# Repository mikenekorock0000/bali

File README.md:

# bali

マーダーミステリー自動進行アプリ「マダミス GM」

## 実機用 APK

**最新:** [madamis_app/dist/madamis-gm-v1.1.0+5.apk](madamis_app/dist/madamis-gm-v1.1.0%2B5.apk)（v1.1.0+5・Android WebView 修正同梱）

互換用: [madamis_app/dist/madamis-gm-release.apk](madamis_app/dist/madamis-gm-release.apk)（常に最新版と同一）

> `main` ブランチの `madamis_app/dist/` に常に置く。再ビルド時は `bash madamis_app/tool/build_release_apk.sh`

## プロジェクト

- アプリ: [madamis_app/](madamis_app/)
- 設計書: [docs/DESIGN.md](docs/DESIGN.md)
- Kindle ダッシュボード: [kindle_dashboard/](kindle_dashboard/)（Fire タブレットで YouTube ライブ・カラー版: [FIRE_SETUP.md](kindle_dashboard/FIRE_SETUP.md)）（**次にやること: [NEXT_STEPS.md](kindle_dashboard/NEXT_STEPS.md)**／NAS 設置: [NAS_SETUP.md](kindle_dashboard/NAS_SETUP.md)・[dist/](kindle_dashboard/dist/)）（調査・脱獄手順: [docs/kindle-dashboard/](docs/kindle-dashboard/README.md)）

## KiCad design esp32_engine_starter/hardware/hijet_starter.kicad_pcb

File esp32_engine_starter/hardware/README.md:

# 基板（ESP32 DevKit V1 30ピン キャリア）

**ESP32 DevKit V1 互換（30 ピン、HW-394、列間 25.4mm）を直接はんだ付けする**、2 層の基板です。部品は TVS（表面実装 4 個）以外すべてリード部品です。
38 ピンの ESP32-DevKitC はピン配置が違うので付けられません。

| 項目 | 内容 |
|---|---|
| 外形 | 98 × 90 mm（100 × 100 mm 以内なので JLCPCB の最安価格）、角に M3 取付穴 ×4 |
| 部品 | 抵抗・ダイオードは足の間隔 5.08 mm で立てて実装。出力の TVS だけ表面実装（SMB、はんだごてで付けられる大きさ） |
| ESP32 | ソケットを使わず直接はんだ付け（振動でソケットが緩むのを防ぐ）。ESP32 の下（隙間 約 2.5mm）には部品を置かない |
| 層 | 2 層（両面に GND ベタ） |
| 最小パターン幅 / 間隔 | 0.4 mm / 0.3 mm（電源系は 1.0 mm） |
| 最小穴径 | 0.4 mm（ビア） |
| 検証 | DRC・ピン照合・部品の収まり・回路シミュレーション・製造データ照合すべて合格。詳しくは [VERIFICATION.md](VERIFICATION.md) |

## 発注するファイル

- **`hijet_starter_gerber.zip`** … ガーバー＋ドリル一式。JLCPCB などにそのままアップロードします。
- 発注時の設定：2 層、FR-4、板厚 1.6 mm、銅厚 1 oz、表面処理は HASL（鉛フリー）、レジストは緑、シルクは白。
- **部品表 `bom.csv`** … 部品ごとに秋月電子通商の商品ページの URL と、買う数を載せています（全部品が秋月でそろいます）。

> **発注前に必ず確認してください。** `hijet_starter_1to1.pdf` を**原寸（100%・拡大縮小なし）**で印刷し、
> 実物の ESP32 ボードのピンが J5・J6 の穴の位置に合うこと、端子台・ブザー・DC-DC の足が穴に合うことを確かめてください。
> 列の間隔 25.4 mm は、購入したボードをノギスで測った値（外側どうし 26.0 mm）と一致しています。

## 回路

| ブロック | 内容 |
|---|---|
| 電源 | J1「+12V」→ F1 ポリスイッチ MF-RX110/72 または RXEF110（1.1A・72V）→ D1 SB340LS（3A、逆接保護）→ D2 P4KE15A ＋ D12 P4KE6.8CA（直列でサージ吸収）・C1 100µF 50V → U1 M78AR05-1（5V 1A、入力 6.5〜32V）→ C2 100µF・C3 0.1µF → ESP32 の 5V ピン |
| 電圧測定 | ヒューズの後ろの 12V → R1 100k / R2 10k で分圧 → GPIO34（16V で 1.45V、9V で 0.82V＝ADC の精度のよい範囲内）。C4 0.1µF でノイズ除去、D3 BAT43 で 3.3V を超えないようクランプ |
| 絶縁出力 ×4 | GPIO25 / 26 / 27 / 32 → 330Ω → PC817（U2〜U5、VCEO 80V）の LED。トランジスタ側を J2 に出す（ESP32 とは電気的に絶縁、各 50mA 以下）。**端子の 2 本の間に双方向 TVS SMBJ45CA（D8〜D11）** |
| 絶縁入力 ×3 | J3 の IN+ → 3.3k → PC817（U6〜U8）→ IN−。1N4148 で逆電圧を保護。出力は GPIO33 / GPIO35 / GPIO36（10k で 3.3V にプルアップ、信号ありで LOW）。3ch 目は ACC（キー ON）検知用。35V まで耐える |
| OBD-II（CAN） | MCP2562FD（U9）。VDD=5V、VIO=3.3V。TXD=GPIO18、RXD=GPIO19。STBY は R15 10k で 3.3V に引いて**既定は待機（車の CAN に一切関与しない）**、GPIO4 を LOW にしたときだけ動作。CAN-H / CAN-L を J7 へ（終端抵抗は付けない） |
| ブザー | GPIO13 → R13 1k → 2SC1815 → 5V 自励式ブザー。R14 10k で起動時は確実に OFF、D7 1N4148 で逆起電力を吸収 |
| GPS | J8：GND / 3V3 / GPS RX（GPIO17 から）/ GPS TX（GPIO16 へ） |
| I2C | J4：GND / 3V3 / SCL(GPIO22) / SDA(GPIO21)。0.96 インチ OLED（SSD1306）モジュールと同じピンの並び |

### 車載向けの保護

| 想定するもの | 対策 |
|---|---|
| バッテリーの逆接続 | D1 SB340LS が電流を止める。入力は 1N4148 で LED を守る。電圧測定は R1 100k で電流を制限 |
| 配線のショート・過電流 | F1 ポリスイッチ（自己復帰型）。トリップするまでの最大 2.2A を流しても D1（3A）は耐える。車両側にもヒューズを入れる |
| 電源ラインのサージ（ノイズ、オルタネーターの急な負荷変動） | D2 P4KE15A と D12 P4KE6.8CA の直列で約 30V 以下に抑える（DC-DC の上限 32V）。18.6V までは導通しない。長く続くときは F1 が切れて止まる |
| 出力の配線から入るサージ、リレーのコイルの逆起電力 | D8〜D11 SMBJ45CA（双方向）が 72.7V 以下に抑える（フォトカプラの上限 80V） |
| 入力の配線のサージ | 3.3k で電流を制限（35V でも LED 10mA、抵抗の発熱は短時間の許容内） |
| 振動 | ESP32 をソケットでなく直接はんだ付け。電解コンデンサは背の低いもの（C2）を使う。基板は M3 スペーサー 4 本で固定 |

**守れないもの**：24V でのジャンプスタート（トラック用の救援）では D2 が導通して F1 が切れ、装置は止まります（壊れるのを防ぐ動作）。続くと D2 が壊れることがあり、その場合は D2 を交換します。

## 端子の使い方

端子台はすべて 5.08mm ピッチです。J2 は 2P を 4 個、J3 は 2P を 3 個、横にスライドさせて連結してから基板に挿します。

| 端子 | ピン | つなぐ先 |
|---|---|---|
| J1 | +12V | ヒューズ電源（常時電源）。車両側にもヒューズを入れる |
|  | GND | ボディアース |
|  | OUT | ヒューズ通過後の 12V（予備入力の IN+ 用） |
| J2 | LOCK − / + | 車両の施錠信号（GND に落とすと施錠するタイプ）。＋を信号線、−を GND へ。線は配線図か取付店で必ず確認する。**＋と−を逆につながない**（フォトカプラは逆向きの電圧に 6V までしか耐えない） |
|  | OUT2〜OUT4 − / + | 汎用。作業灯などはリレーモジュールの入力につなぐ（直接は駆動できない） |
| J3 | IN1 + / − | 例：ドアの開閉信号（スイッチが GND に落ちるタイプ）は、IN+ を J1 の「OUT」へ、IN− をドアの信号線へつなぐ |
|  | ACC + / − | ACC（キー ON で 12V）の線を ACC+ に、ACC− を GND に |
| J7 | CAN H / L / G | OBD-II コネクタの 6 番（CAN-H）、14 番（CAN-L）、4・5 番（GND）。市販の OBD-II 延長ケーブルを切って使うと楽 |
| J8 | GND 3V3 GPS RX / TX（上から） | NEO-6M など UART の GPS モジュール。GPS RX の端子をモジュールの RX に、GPS TX の端子をモジュールの TX につなぐ |
| J4 | GND 3V3 SCL SDA（上から） | OLED や温度センサー（BME280 など）。四角いパッドが GND |

## 組み立て

部品表は `bom.csv` です。部品番号は基板のシルク印刷と同じです。

1. **最初に TVS（D8〜D11）** を付けます。表面実装なので、片方のパッドに少しはんだを盛り、ピンセットで部品を押さえて温め、反対側を付けます。向きはありません（双方向）。
2. 背の低い部品から順にはんだ付けします：抵抗 → ダイオード → フォトカプラ・MCP2562 → セラミックコンデンサ → トランジスタ → ピンヘッダー（J4・J8）→ ポリスイッチ → 電解コンデンサ → ブザー → 端子台 → DC-DC。
3. **向きのある部品に注意してください。**
   - ポリスイッチ（F1）：本体が大きい（幅 12.8mm）ので、基板の上の端に横向きに付ける。向きはない。
   - ダイオード（D1〜D7、D12）：立てて付ける。本体を丸いシルクの穴の上に立て、**帯（カソード）を上にして**、上から折り返した足を「K」の四角いパッドへ。D12（P4KE6.8CA）だけは双方向なので向きはどちらでもよい。
   - 電解コンデンサ（C1・C2）：長い足（＋）を、シルクの「+」がある四角いパッドに。
   - フォトカプラ（U2〜U8）：本体の 1 番ピンの丸印を、四角いパッドに合わせる。
   - M78AR05-1（U1）：1 番ピン（Vin）を四角いパッドに。
   - MCP2562（U9）：本体の 1 番ピンの丸印（切り欠き側）を四角いパッドに。
   - 2SC1815（Q1）：左のパッドから E-C-B。シルクの半円が本体の丸い側。足の並びが違うトランジスタは使わない。
   - 抵抗：立てて付ける。どちら向きでもよい（本体を丸いシルクの穴の上に立てる）。
   - ブザー（BZ1）：＋表示の足（長い足）を「+」の四角いパッドに。
4. **ESP32 を付ける前に**、J1 に 12V をつないで、J5 の 15 番ピン（いちばん下、ESP32 の VIN）と GND の間が約 5V になることをテスターで確認します。
5. ESP32 ボードを **USB コネクタが基板の下側（「USB cable keep clear」の文字の方）**、VIN の列が左（J5）に来る向きで挿し、ボードを基板に押し付けたまま（ピンの樹脂が基板に当たるまで）四隅のピンを先にはんだ付けしてから、残りのピンを付けます。直接はんだ付けなので、後から外すのは大変です。向きを 2 回確かめてから付けてください。
6. ESP32 に USB で書き込むときは、J1 の 12V を外してください（両方から同時に給電しないため）。USB ケーブルのプラグは基板の上を通るので、「USB cable keep clear」の場所には何も置かないでください。

## 作り直すとき

`./build.sh` は、生成のあとに DRC・ピン照合（`check_pins.py`）・部品の収まり（`check_mech.py`）・回路シミュレーション（`sim/`、ngspice が必要）・製造データ照合（`check_fab.py`）を実行し、1 つでも問題があれば止まります。

```
./build.sh   # 生成 → 検証（DRC・ピン・収まり・回路・製造データ）→ ガーバー/ドリル → zip → BOM → 原寸 PDF → プレビュー
```

KiCad 7（`kicad-cli` と Python の `pcbnew`）と numpy が必要です。部品の位置と接続先は `gen_pcb.py` の上の方にまとめてあります。
配線は簡易オートルーターで引いているので、部品を動かしたら必ず `./build.sh` で DRC を通してください。

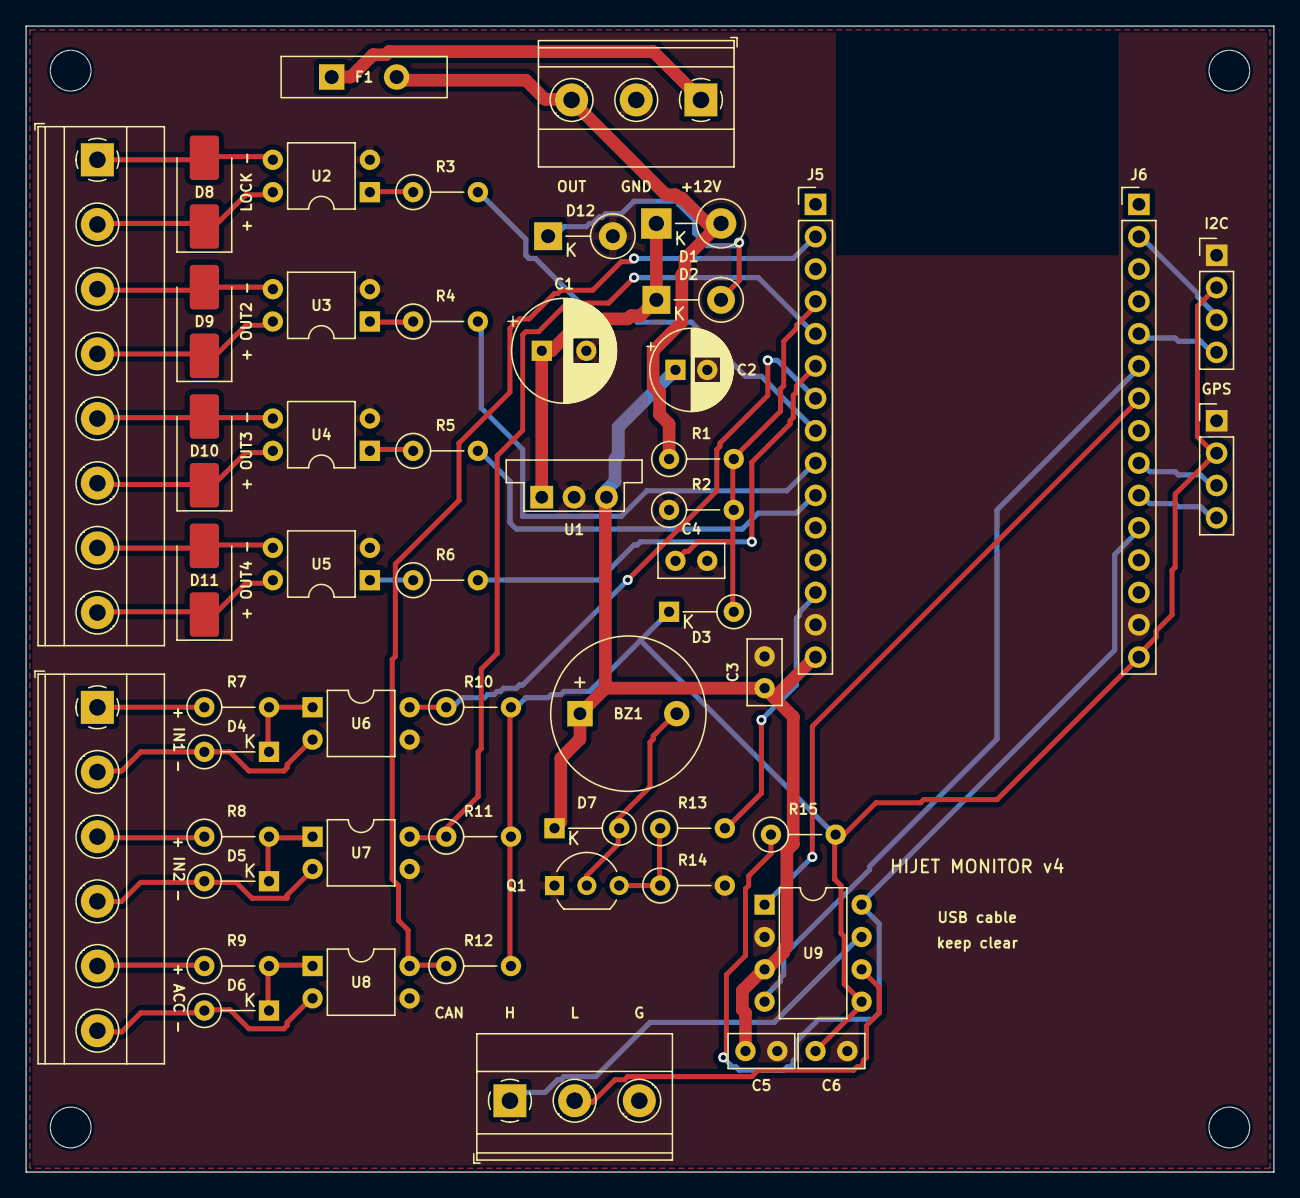
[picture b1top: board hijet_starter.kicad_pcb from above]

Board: 2 copper layers, 98.0 x 90.0 mm, 57 parts (0 on the bottom side), 48 nets.

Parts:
BZ1: Buzzer 5V 12mm; Buzzer_12x9.5RM7.6
C1: 100uF 50V; CP_Radial_D8.0mm_P3.50mm
C2: 100uF 16V; CP_Radial_D6.3mm_P2.50mm
C3, C4, C5, C6: 0.1uF; C_Disc_D5.0mm_W2.5mm_P2.50mm
D1: SB340LS; D_DO-15_P5.08mm_Vertical_KathodeUp
D2: P4KE15A; D_DO-41_SOD81_P5.08mm_Vertical_KathodeUp
D3: BAT43; D_DO-35_SOD27_P5.08mm_Vertical_KathodeUp
D4, D5, D6, D7: 1N4148; D_DO-35_SOD27_P5.08mm_Vertical_KathodeUp
D8, D9, D10, D11: SMBJ45CA; D_SMB_Handsoldering
D12: P4KE6.8CA; D_DO-41_SOD81_P5.08mm_Vertical_KathodeUp
F1: PTC 1.1A; PTC_Radial_W12.8mm_T3.0mm_P5.10mm
H1, H2, H3, H4: M3; MountingHole_3.2mm_M3
J1: 12V IN; TerminalBlock_Phoenix_MKDS-1,5-3-5.08_1x03_P5.08mm_Horizont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
J2: OUT; TerminalBlock_Phoenix_MKDS-1,5-8-5.08_1x08_P5.08mm_Horizont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
J3: IN; TerminalBlock_Phoenix_MKDS-1,5-6-5.08_1x06_P5.08mm_Horizont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
J4: I2C; PinHeader_1x04_P2.54mm_Vertical
J5: ESP32 VIN row; PinHeader_1x15_P2.54mm_Vertical
J6: ESP32 3V3 row; PinHeader_1x15_P2.54mm_Vertical
J7: OBD-II CAN; TerminalBlock_Phoenix_MKDS-1,5-3-5.08_1x03_P5.08mm_Horizont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
J8: GPS; PinHeader_1x04_P2.54mm_Vertical
Q1: 2SC1815; TO-92_Inline_Wide
R1: 100k; R_Axial_DIN0207_L6.3mm_D2.5mm_P5.08mm_Vertical
R2, R10, R11, R12, R14, R15: 10k; R_Axial_DIN0207_L6.3mm_D2.5mm_P5.08mm_Vertical
R3, R4, R5, R6: 330; R_Axial_DIN0207_L6.3mm_D2.5mm_P5.08mm_Vertical
R7, R8, R9: 3.3k; R_Axial_DIN0207_L6.3mm_D2.5mm_P5.08mm_Vertical
R13: 1k; R_Axial_DIN0207_L6.3mm_D2.5mm_P5.08mm_Vertical
U1: M78AR05-1; Converter_DCDC_Murata_OKI-78SR_Vertical
U2, U3, U4, U5, U6, U7, U8: PC817; DIP-4_W7.62mm
U9: MCP2562-E/P; DIP-8_W7.62mm

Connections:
12V_F: D1.2, F1.2, J1.3, R1.1
12V_P: C1.1, D1.1, D2.1, U1.1
+3V3: C6.1, D3.1, J4.2, J6.15, J8.2, R10.2, R11.2, R12.2, R15.2, U9.5
+5V: BZ1.1, C2.1, C3.1, C5.1, D7.1, J5.15, U1.3, U9.3
BATT: F1.1, J1.1
BZN: BZ1.2, D7.2, Q1.2
CANH: J7.1, U9.7
CANL: J7.2, U9.6
G13: J5.13, R13.2
G16: J6.10, J8.4
G17: J6.9, J8.3
G18: J6.7, U9.1
G19: J6.6, U9.4
G25: J5.8, R3.2
G26: J5.9, R4.2
G27: J5.10, R5.2
G32: J5.6, R6.2
G33: J5.7, R10.1, U6.4
G35: J5.5, R11.1, U7.4
G36: J5.2, R12.1, U8.4
GND: C1.2, C2.2, C3.2, C4.2, C5.2, C6.2, D12.2, J1.2, J4.1, J5.14, J6.14, J7.3, J8.1, Q1.1, R2.1, R14.2, U1.2, U2.2, U3.2, U4.2, U5.2, U6.3, U7.3, U8.3, U9.2
IN1A: D4.1, R7.2, U6.1
IN1N: D4.2, J3.2, U6.2
IN1P: J3.1, R7.1
IN2A: D5.1, R8.2, U7.1
IN2N: D5.2, J3.4, U7.2
IN2P: J3.3, R8.1
IN3A: D6.1, R9.2, U8.1
IN3N: D6.2, J3.6, U8.2
IN3P: J3.5, R9.1
LED1: R3.1, U2.1
LED2: R4.1, U3.1
LED3: R5.1, U4.1
LED4: R6.1, U5.1
O1C: D8.1, J2.2, U2.4
O1E: D8.2, J2.1, U2.3
O2C: D9.1, J2.4, U3.4
O2E: D9.2, J2.3, U3.3
O3C: D10.1, J2.6, U4.4
O3E: D10.2, J2.5, U4.3
O4C: D11.1, J2.8, U5.4
O4E: D11.2, J2.7, U5.3
QB: Q1.3, R13.1, R14.1
SCL: J4.3, J6.2
SDA: J4.4, J6.5
STBY: J6.11, R15.1, U9.8
TVSM: D2.2, D12.1
VSENSE: C4.1, D3.2, J5.4, R1.2, R2.2

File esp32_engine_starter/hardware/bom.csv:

部品数,部品番号,値,内容,買う数,購入先,URL
1,BZ1,Buzzer 5V 12mm,電子ブザー（発振回路内蔵）5V φ12mm UGCM1205XP。足の間隔 7.6mm を原寸 PDF で確認,1,秋月,https://akizukidenshi.com/catalog/g/g109800/
1,C1,100uF 50V,電解コンデンサ 100µF 50V φ8mm 足の間隔 3.5mm（105℃、Rubycon PX）,1,秋月,https://akizukidenshi.com/catalog/g/g117905/
1,C2,100uF 16V,電解コンデンサ 100µF 16V φ6.3mm 高さ 5mm 足の間隔 2.5mm（105℃）,1,秋月,https://akizukidenshi.com/catalog/g/g105002/
4,C3 C4 C5 C6,0.1uF,積層セラミック 0.1µF 50V X7R 足の間隔 2.5mm（村田製作所）,4,秋月,https://akizukidenshi.com/catalog/g/g113582/
1,D1,SB340LS,ショットキーダイオード SB340LS 40V 3A（DO-15、立てて実装）逆接保護,1,秋月,https://akizukidenshi.com/catalog/g/g107788/
1,D2,P4KE15A,TVS ダイオード P4KE15A 400W 単方向（DO-41、立てて実装）。P4KE6.8CA と直列で電源のサージ吸収,1,秋月,https://akizukidenshi.com/catalog/g/g129633/
1,D3,BAT43,小信号ショットキー BAT43（DO-35）電圧測定入力のクランプ,1,秋月,https://akizukidenshi.com/catalog/g/g113907/
4,D4 D5 D6 D7,1N4148,小信号ダイオード 1N4148（DO-35）入力の逆電圧保護・ブザーの逆起電力吸収,4,秋月,https://akizukidenshi.com/catalog/g/g100941/
4,D8 D9 D10 D11,SMBJ45CA,TVS ダイオード SMBJ45CA 双方向 600W（表面実装 SMB）出力端子のサージ保護。向きはない,4,秋月,https://akizukidenshi.com/catalog/g/g107410/
1,D12,P4KE6.8CA,TVS ダイオード P4KE6.8CA 400W 双方向（DO-41、立てて実装、向きなし）。P4KE15A と直列,1,秋月,https://akizukidenshi.com/catalog/g/g129631/
1,F1,PTC 1.1A,リセッタブルヒューズ Bourns MF-RX110/72（保持 1.1A・トリップ 2.2A・72V、幅 10.8mm・足 0.81mm・間隔 5.1mm）。Littelfuse RXEF110（秋月 101356）でも可。RUEF 系（30V）は不可,1,秋月,https://akizukidenshi.com/catalog/g/g113585/
1,J1,12V IN,端子台 3P 5.08mm TB112-2-3-E-1（ねじが上、電線は横から入るタイプ）,1,秋月,https://akizukidenshi.com/catalog/g/g101310/
1,J2,OUT,端子台 2P 5.08mm TB112-2-2-E-1 を 4 個連結して 8P にする（電線は横から入るタイプ）,4,秋月,https://akizukidenshi.com/catalog/g/g101308/
1,J3,IN,端子台 2P 5.08mm TB112-2-2-E-1 を 3 個連結して 6P にする,3,秋月,https://akizukidenshi.com/catalog/g/g101308/
1,J4,I2C,ピンヘッダー 1×4 2.54mm（1×40 を切って使う。GPS 用と合わせて 1 本）,1 本（1×40）,秋月,https://akizukidenshi.com/catalog/g/g100167/
1,J5,ESP32 VIN row,ESP32 DevKit V1 30 ピン（購入済み）を直接はんだ付けする。ピンが付いていないボードはピンヘッダー 1×15 を 2 本付ける,,購入済み,
1,J6,ESP32 3V3 row,（同上）,,,
1,J7,OBD-II CAN,端子台 3P 5.08mm TB112-2-3-E-1,1,秋月,https://akizukidenshi.com/catalog/g/g101310/
1,J8,GPS,ピンヘッダー 1×4 2.54mm（上の 1×40 から切り出す）,,,
1,Q1,2SC1815,NPN トランジスタ 2SC1815（TO-92、足の並び E-C-B）,1,秋月,https://akizukidenshi.com/catalog/g/g117089/
1,R1,100k,抵抗 100kΩ 1/4W（立てて実装）,1 袋（100 本）,秋月,https://akizukidenshi.com/catalog/g/g125104/
6,R2 R10 R11 R12 R14 R15,10k,抵抗 10kΩ 1/4W（立てて実装）。R2（電圧測定）も 10k,1 袋（100 本）,秋月,https://akizukidenshi.com/catalog/g/g125103/
4,R3 R4 R5 R6,330,抵抗 330Ω 1/4W（立てて実装）,1 袋（100 本）,秋月,https://akizukidenshi.com/catalog/g/g125331/
3,R7 R8 R9,3.3k,抵抗 3.3kΩ 1/4W（立てて実装）,1 袋（100 本）,秋月,https://akizukidenshi.com/catalog/g/g125332/
1,R13,1k,抵抗 1kΩ 1/4W（立てて実装）,1 袋（100 本）,秋月,https://akizukidenshi.com/catalog/g/g125102/
1,U1,M78AR05-1,DC-DC 5V 1A MINMAX M78AR05-1（三端子レギュレーター互換、入力 6.5〜32V）,1,秋月,https://akizukidenshi.com/catalog/g/g113536/
7,U2 U3 U4 U5 U6 U7 U8,PC817,フォトカプラ PC817X3NSZ1B（DIP-4、VCEO 80V、CTR 200〜400%）,7,秋月,https://akizukidenshi.com/catalog/g/g113765/
1,U9,MCP2562-E/P,CAN トランシーバー MCP2562FD-E/P（DIP-8）。MCP2561 は 5 番ピンが違うので不可,1,秋月,https://akizukidenshi.com/catalog/g/g114383/
,取付,,スペーサー M3 10mm（オス・メス）TP-10,4,秋月,https://akizukidenshi.com/catalog/g/g107566/
,取付,,なべ小ねじ M3×10（スペーサーの固定用）,1 袋,秋月,https://akizukidenshi.com/catalog/g/g110253/
